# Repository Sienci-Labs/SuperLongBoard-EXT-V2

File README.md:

# SuperLongBoard EXT V2

The **SuperLongBoard EXT V2 (SLB-EXT V2)** is Sienci Labs’ next-generation CNC controller developed for the AltMill platform.

## Key Features

* grblHAL-based firmware
* Four-axis motion control
* Closed-loop stepper motor support
* USB connectivity
* SD card support
* Spindle, router and laser support
* Tool-length sensor support
* Auto-squaring
* Advanced breakout-board expansion

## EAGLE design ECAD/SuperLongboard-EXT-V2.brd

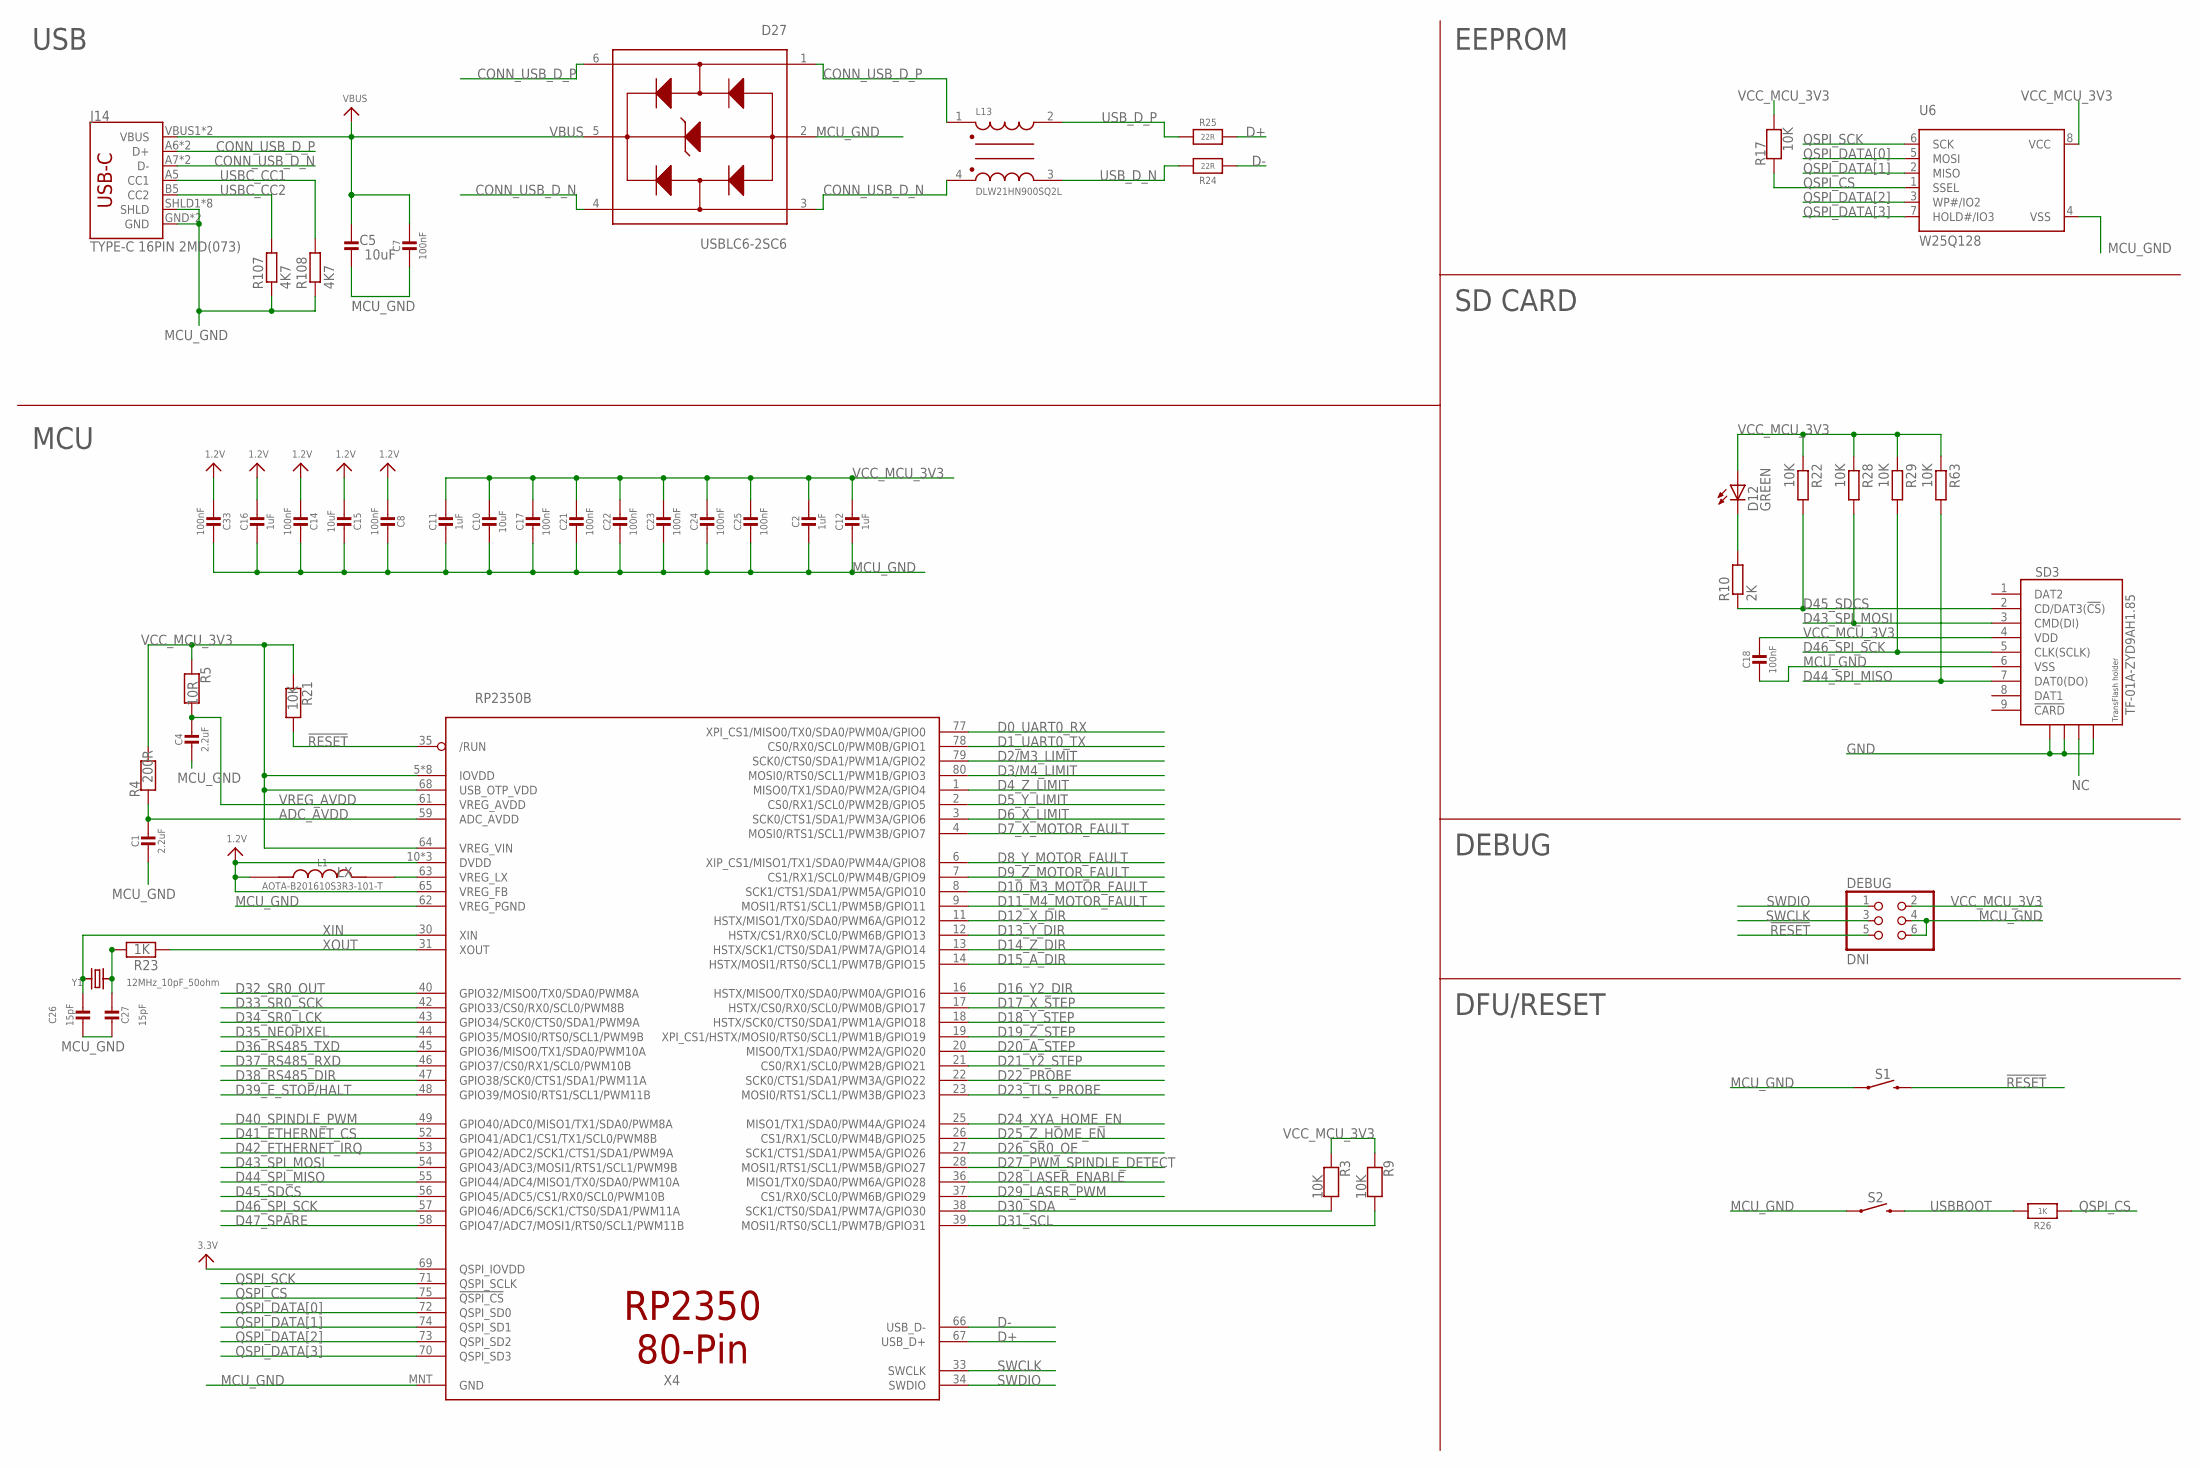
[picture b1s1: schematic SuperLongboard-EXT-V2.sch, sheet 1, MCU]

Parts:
C1, C4: 2.2uF; 0603-NO
C2, C11, C12, C16: 1uF; 0603-NO
C5, C10, C15: 10uF; _1206
C7, C8, C14, C17, C18, C21, C22, C23, C24, C25, C33: 100nF; 0603-NO
C26, C27: 15pF; 0603-NO
D12: GREEN; CHIP-LED0805
D27: USBLC6-2SC6; SOT95P280X145-6N
DEBUG: DNI; 2X03
J14: TYPE-C 16PIN 2MD(073); USB-C-16P
L1: AOTA-B201610S3R3-101-T; INDUCTOR-0806; LCSC_PART C42411119
L13: DLW21HN900SQ2L; FIL_DLW21HN900SQ2L
R3, R9: 10K; 0603-NO
R4: 200R; 0603-NO
R5: 10R; 0603-NO
R10: 2K; R0603
R17, R21: 10K; _0603
R22, R28, R29, R63: 10K; R0603
R23, R26: 1K; _0603
R24, R25: 22R; 0603-NO
R107, R108: 4K7; R0603
S1, S2: ZX-QC36-4.3TPWD; TACTILE_SWITCH_SMD_6.0X3.5MM
SD3: TF-01A-ZYD9AH1.85; TF-PULL
U6: W25Q128; SOIC8_208MIL
X4: RP2350B; QFN80
Y1: 12MHz_10pF_50ohm; CRYSTAL_3.2X2.5

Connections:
1.2V: C8.2, C14.2, C15.2, C16.1, C33.2, L1.1, X4.10 (DVDD), X4.32 (DVDD), X4.51 (DVDD), X4.65 (VREG_FB)
!RESET: DEBUG.5, R21.2, S1.2, X4.35 (/RUN)
ADC_AVDD: C1.1, R4.1, X4.59 (ADC_AVDD)
CONN_USB_D_N: D27.3 (I/O2_IN), D27.4 (I/O2_OUT), J14.A7 (D-), J14.B7 (D-), L13.4
CONN_USB_D_P: D27.1 (I/O1_IN), D27.6 (I/O1_OUT), J14.A6 (D+), J14.B6 (D+), L13.1
D0_UART0_RX: X4.77 (XPI_CS1/MISO0/TX0/SDA0/PWM0A/GPIO0); also elsewhere on the board
D1_UART0_TX: X4.78 (CS0/RX0/SCL0/PWM0B/GPIO1); also elsewhere on the board
D2/M3_LIMIT: X4.79 (SCK0/CTS0/SDA1/PWM1A/GPIO2); also elsewhere on the board
D3/M4_LIMIT: X4.80 (MOSI0/RTS0/SCL1/PWM1B/GPIO3); also elsewhere on the board
D4_Z_LIMIT: X4.1 (MISO0/TX1/SDA0/PWM2A/GPIO4); also elsewhere on the board
D5_Y_LIMIT: X4.2 (CS0/RX1/SCL0/PWM2B/GPIO5); also elsewhere on the board
D6_X_LIMIT: X4.3 (SCK0/CTS1/SDA1/PWM3A/GPIO6); also elsewhere on the board
D7_X_MOTOR_FAULT: X4.4 (MOSI0/RTS1/SCL1/PWM3B/GPIO7); also elsewhere on the board
D8_Y_MOTOR_FAULT: X4.6 (XIP_CS1/MISO1/TX1/SDA0/PWM4A/GPIO8); also elsewhere on the board
D9_Z_MOTOR_FAULT: X4.7 (CS1/RX1/SCL0/PWM4B/GPIO9); also elsewhere on the board
D10_M3_MOTOR_FAULT: X4.8 (SCK1/CTS1/SDA1/PWM5A/GPIO10); also elsewhere on the board
D11_M4_MOTOR_FAULT: X4.9 (MOSI1/RTS1/SCL1/PWM5B/GPIO11); also elsewhere on the board
D12_X_DIR: X4.11 (HSTX/MISO1/TX0/SDA0/PWM6A/GPIO12); also elsewhere on the board
D13_Y_DIR: X4.12 (HSTX/CS1/RX0/SCL0/PWM6B/GPIO13); also elsewhere on the board
D14_Z_DIR: X4.13 (HSTX/SCK1/CTS0/SDA1/PWM7A/GPIO14); also elsewhere on the board
D15_A_DIR: X4.14 (HSTX/MOSI1/RTS0/SCL1/PWM7B/GPIO15); also elsewhere on the board
D16_Y2_DIR: X4.16 (HSTX/MISO0/TX0/SDA0/PWM0A/GPIO16); also elsewhere on the board
D17_X_STEP: X4.17 (HSTX/CS0/RX0/SCL0/PWM0B/GPIO17); also elsewhere on the board
D18_Y_STEP: X4.18 (HSTX/SCK0/CTS0/SDA1/PWM1A/GPIO18); also elsewhere on the board
D19_Z_STEP: X4.19 (XPI_CS1/HSTX/MOSI0/RTS0/SCL1/PWM1B/GPIO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); also elsewhere on the board
D20_A_STEP: X4.20 (MISO0/TX1/SDA0/PWM2A/GPIO20); also elsewhere on the board
D21_Y2_STEP: X4.21 (CS0/RX1/SCL0/PWM2B/GPIO21); also elsewhere on the board
D22_PROBE: X4.22 (SCK0/CTS1/SDA1/PWM3A/GPIO22); also elsewhere on the board
D23_TLS_PROBE: X4.23 (MOSI0/RTS1/SCL1/PWM3B/GPIO23); also elsewhere on the board
D24_XYA_HOME_EN: X4.25 (MISO1/TX1/SDA0/PWM4A/GPIO24); also elsewhere on the board
D25_Z_HOME_EN: X4.26 (CS1/RX1/SCL0/PWM4B/GPIO25); also elsewhere on the board
D26_SR0_OE: X4.27 (SCK1/CTS1/SDA1/PWM5A/GPIO26); also elsewhere on the board
D27_PWM_SPINDLE_DETECT: X4.28 (MOSI1/RTS1/SCL1/PWM5B/GPIO27); also elsewhere on the board
D28_LASER_ENABLE: X4.36 (MISO1/TX0/SDA0/PWM6A/GPIO28); also elsewhere on the board
D29_LASER_PWM: X4.37 (CS1/RX0/SCL0/PWM6B/GPIO29); also elsewhere on the board
D30_SDA: R3.2, X4.38 (SCK1/CTS0/SDA1/PWM7A/GPIO30); also elsewhere on the board
D31_SCL: R9.2, X4.39 (MOSI1/RTS0/SCL1/PWM7B/GPIO31); also elsewhere on the board
D32_SR0_OUT: X4.40 (GPIO32/MISO0/TX0/SDA0/PWM8A); also elsewhere on the board
D33_SR0_SCK: X4.42 (GPIO33/CS0/RX0/SCL0/PWM8B); also elsewhere on the board
D34_SR0_LCK: X4.43 (GPIO34/SCK0/CTS0/SDA1/PWM9A); also elsewhere on the board
D35_NEOPIXEL: X4.44 (GPIO35/MOSI0/RTS0/SCL1/PWM9B); also elsewhere on the board
D36_RS485_TXD: X4.45 (GPIO36/MISO0/TX1/SDA0/PWM10A); also elsewhere on the board
D37_RS485_RXD: X4.46 (GPIO37/CS0/RX1/SCL0/PWM10B); also elsewhere on the board
D38_RS485_DIR: X4.47 (GPIO38/SCK0/CTS1/SDA1/PWM11A); also elsewhere on the board
D39_E_STOP/HALT: X4.48 (GPIO39/MOSI0/RTS1/SCL1/PWM11B); also elsewhere on the board
D40_SPINDLE_PWM: X4.49 (GPIO40/ADC0/MISO1/TX1/SDA0/PWM8A); also elsewhere on the board
D41_ETHERNET_CS: X4.52 (GPIO41/ADC1/CS1/TX1/SCL0/PWM8B); also elsewhere on the board
D42_ETHERNET_IRQ: X4.53 (GPIO42/ADC2/SCK1/CTS1/SDA1/PWM9A); also elsewhere on the board
D43_SPI_MOSI: R28.2, SD3.3 (CMD(DI)), X4.54 (GPIO43/ADC3/MOSI1/RTS1/SCL1/PWM9B); also elsewhere on the board
D44_SPI_MISO: R63.2, SD3.7 (DAT0(DO)), X4.55 (GPIO44/ADC4/MISO1/TX0/SDA0/PWM10A); also elsewhere on the board
D45_SDCS: R10.1, R22.2, SD3.2 (CD/DAT3(!CS!)), X4.56 (GPIO45/ADC5/CS1/RX0/SCL0/PWM10B)
D46_SPI_SCK: R29.2, SD3.5 (CLK(SCLK)), X4.57 (GPIO46/ADC6/SCK1/CTS0/SDA1/PWM11A); also elsewhere on the board
D47_SPARE: X4.58 (GPIO47/ADC7/MOSI1/RTS0/SCL1/PWM11B); also elsewhere on the board
D+: R25.2, X4.67 (USB_D+)
D-: R24.2, X4.66 (USB_D-)
GND: SD3.S1, SD3.S2, SD3.S4; also elsewhere on the board
LX: L1.2, X4.63 (VREG_LX)
MCU_GND: C1.2, C2.2, C4.2, C5.1, C7.2, C8.1, C10.2, C11.2, C12.2, C14.1, C15.1, C16.2, C17.2, C18.2, C21.2, C22.2, C23.2, C24.2, C25.2, C26.1, C27.1, C33.1, D27.2 (GND), DEBUG.4, DEBUG.6, J14.GND, J14.GND2 (GND), J14.SHLD1 (SHLD), J14.SHLD2 (SHLD), J14.SHLD3 (SHLD), J14.SHLD4 (SHLD), J14.SHLD5 (SHLD), J14.SHLD6 (SHLD), J14.SHLD7 (SHLD), J14.SHLD8 (SHLD), R107.1, R108.1, S1.1, S2.1, SD3.6 (VSS), U6.4 (VSS), X4.62 (VREG_PGND), X4.MNT (GND); also elsewhere on the board
unnamed: D12.C, R10.2
unnamed: C27.2, R23.1, Y1.2
NC: SD3.S3
QSPI_CS: R17.1, R26.1, U6.1 (SSEL), X4.75 (!QSPI_CS)
QSPI_DATA[0]: U6.5 (MOSI), X4.72 (QSPI_SD0)
QSPI_DATA[1]: U6.2 (MISO), X4.74 (QSPI_SD1)
QSPI_DATA[2]: U6.3 (WP#/IO2), X4.73 (QSPI_SD2)
QSPI_DATA[3]: U6.7 (HOLD#/IO3), X4.70 (QSPI_SD3)
QSPI_SCK: U6.6 (SCK), X4.71 (QSPI_SCLK)
SWCLK: DEBUG.3, X4.33 (SWCLK)
SWDIO: DEBUG.1, X4.34 (SWDIO)
USBBOOT: R26.2, S2.2
USBC_CC1: J14.A5 (CC1), R108.2
USBC_CC2: J14.B5 (CC2), R107.2
USB_D_N: L13.3, R24.1
USB_D_P: L13.2, R25.1
VBUS: C5.2, C7.1, D27.5 (VBUS), J14.VBUS1 (VBUS), J14.VBUS2 (VBUS); also elsewhere on the board
VCC_MCU_3V3: C2.1, C10.1, C11.1, C12.1, C17.1, C18.1, C21.1, C22.1, C23.1, C24.1, C25.1, D12.A, DEBUG.2, R3.1, R4.2, R5.1, R9.1, R17.2, R21.1, R22.1, R28.1, R29.1, R63.1, SD3.4 (VDD), U6.8 (VCC), X4.5 (IOVDD), X4.15 (IOVDD), X4.24 (IOVDD), X4.29 (IOVDD), X4.41 (IOVDD), X4.50 (IOVDD), X4.60 (IOVDD), X4.64 (VREG_VIN), X4.68 (USB_OTP_VDD), X4.69 (QSPI_IOVDD), X4.76 (IOVDD); also elsewhere on the board
VREG_AVDD: C4.1, R5.2, X4.61 (VREG_AVDD)
XIN: C26.2, X4.30 (XIN), Y1.1
XOUT: R23.2, X4.31 (XOUT)

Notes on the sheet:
USB
MCU
EEPROM
SD CARD
DFU/RESET
DEBUG

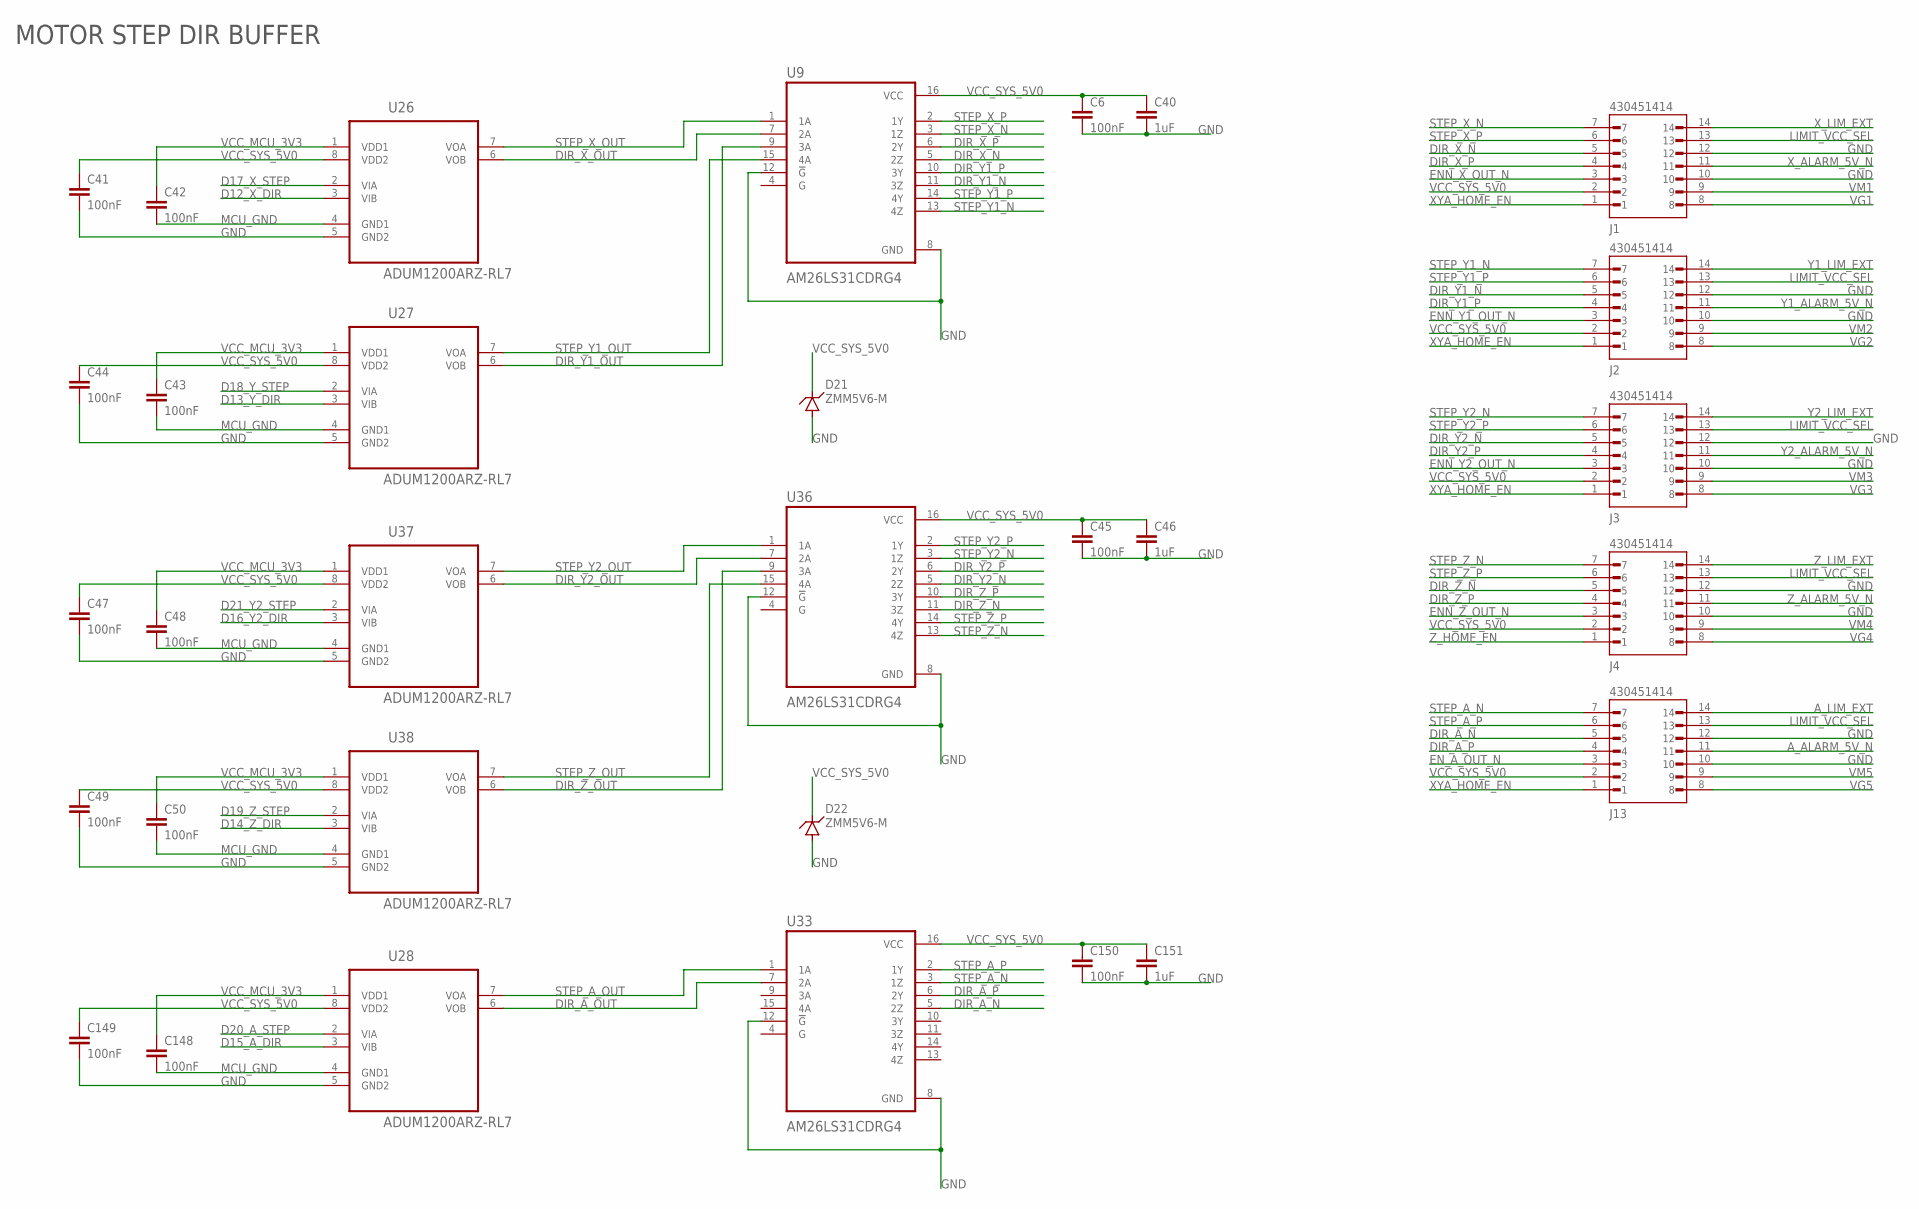
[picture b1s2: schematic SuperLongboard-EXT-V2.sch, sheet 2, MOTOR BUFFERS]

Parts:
C6, C41, C42, C43, C44, C45, C47, C48, C49, C50, C148, C149, C150: 100nF; C0603K
C40, C46, C151: 1uF; C0603K
D21, D22: ZMM5V6-M; MINIMELF
J1, J2, J3, J4, J13: 430451414; MOLEX_430451414
U9, U33, U36: AM26LS31CDRG4; SOIC127P600X175-16N
U26, U27, U28, U37, U38: ADUM1200ARZ-RL7; SOIC127P600X175-8N

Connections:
A_ALARM_5V_N: J13.11; also elsewhere on the board
A_LIM_EXT: J13.14; also elsewhere on the board
D12_X_DIR: U26.3 (VIB); also elsewhere on the board
D13_Y_DIR: U27.3 (VIB); also elsewhere on the board
D14_Z_DIR: U38.3 (VIB); also elsewhere on the board
D15_A_DIR: U28.3 (VIB); also elsewhere on the board
D16_Y2_DIR: U37.3 (VIB); also elsewhere on the board
D17_X_STEP: U26.2 (VIA); also elsewhere on the board
D18_Y_STEP: U27.2 (VIA); also elsewhere on the board
D19_Z_STEP: U38.2 (VIA); also elsewhere on the board
D20_A_STEP: U28.2 (VIA); also elsewhere on the board
D21_Y2_STEP: U37.2 (VIA); also elsewhere on the board
DIR_A_N: J13.5, U33.5 (2Z)
DIR_A_OUT: U28.6 (VOB), U33.7 (2A)
DIR_A_P: J13.4, U33.6 (2Y)
DIR_X_N: J1.5, U9.5 (2Z)
DIR_X_OUT: U9.7 (2A), U26.6 (VOB)
DIR_X_P: J1.4, U9.6 (2Y)
DIR_Y1_N: J2.5, U9.11 (3Z)
DIR_Y1_OUT: U9.9 (3A), U27.6 (VOB)
DIR_Y1_P: J2.4, U9.10 (3Y)
DIR_Y2_N: J3.5, U36.5 (2Z)
DIR_Y2_OUT: U36.7 (2A), U37.6 (VOB)
DIR_Y2_P: J3.4, U36.6 (2Y)
DIR_Z_N: J4.5, U36.11 (3Z)
DIR_Z_OUT: U36.9 (3A), U38.6 (VOB)
DIR_Z_P: J4.4, U36.10 (3Y)
ENN_X_OUT_N: J1.3; also elsewhere on the board
ENN_Y1_OUT_N: J2.3; also elsewhere on the board
ENN_Y2_OUT_N: J3.3; also elsewhere on the board
ENN_Z_OUT_N: J4.3; also elsewhere on the board
EN_A_OUT_N: J13.3; also elsewhere on the board
GND: C6.2, C40.2, C41.2, C44.2, C45.2, C46.2, C47.2, C49.2, C149.2, C150.2, C151.2, D21.A, D22.A, J1.10, J1.12, J2.10, J2.12, J3.10, J3.12, J4.10, J4.12, J13.10, J13.12, U9.8 (GND), U9.12 (!G), U26.5 (GND2), U27.5 (GND2), U28.5 (GND2), U33.8 (GND), U33.12 (!G), U36.8 (GND), U36.12 (!G), U37.5 (GND2), U38.5 (GND2); also elsewhere on the board
LIMIT_VCC_SEL: J1.13, J2.13, J3.13, J4.13, J13.13; also elsewhere on the board
MCU_GND: C42.2, C43.2, C48.2, C50.2, C148.2, U26.4 (GND1), U27.4 (GND1), U28.4 (GND1), U37.4 (GND1), U38.4 (GND1); also elsewhere on the board
STEP_A_N: J13.7, U33.3 (1Z)
STEP_A_OUT: U28.7 (VOA), U33.1 (1A)
STEP_A_P: J13.6, U33.2 (1Y)
STEP_X_N: J1.7, U9.3 (1Z)
STEP_X_OUT: U9.1 (1A), U26.7 (VOA)
STEP_X_P: J1.6, U9.2 (1Y)
STEP_Y1_N: J2.7, U9.13 (4Z)
STEP_Y1_OUT: U9.15 (4A), U27.7 (VOA)
STEP_Y1_P: J2.6, U9.14 (4Y)
STEP_Y2_N: J3.7, U36.3 (1Z)
STEP_Y2_OUT: U36.1 (1A), U37.7 (VOA)
STEP_Y2_P: J3.6, U36.2 (1Y)
STEP_Z_N: J4.7, U36.13 (4Z)
STEP_Z_OUT: U36.15 (4A), U38.7 (VOA)
STEP_Z_P: J4.6, U36.14 (4Y)
VCC_MCU_3V3: C42.1, C43.1, C48.1, C50.1, C148.1, U26.1 (VDD1), U27.1 (VDD1), U28.1 (VDD1), U37.1 (VDD1), U38.1 (VDD1); also elsewhere on the board
VCC_SYS_5V0: C6.1, C40.1, C41.1, C44.1, C45.1, C46.1, C47.1, C49.1, C149.1, C150.1, C151.1, D21.C, D22.C, J1.2, J2.2, J3.2, J4.2, J13.2, U9.16 (VCC), U26.8 (VDD2), U27.8 (VDD2), U28.8 (VDD2), U33.16 (VCC), U36.16 (VCC), U37.8 (VDD2), U38.8 (VDD2); also elsewhere on the board
VG1: J1.8; also elsewhere on the board
VG2: J2.8; also elsewhere on the board
VG3: J3.8; also elsewhere on the board
VG4: J4.8; also elsewhere on the board
VG5: J13.8; also elsewhere on the board
VM1: J1.9; also elsewhere on the board
VM2: J2.9; also elsewhere on the board
VM3: J3.9; also elsewhere on the board
VM4: J4.9; also elsewhere on the board
VM5: J13.9; also elsewhere on the board
XYA_HOME_EN: J1.1, J2.1, J3.1, J13.1; also elsewhere on the board
X_ALARM_5V_N: J1.11; also elsewhere on the board
X_LIM_EXT: J1.14; also elsewhere on the board
Y1_ALARM_5V_N: J2.11; also elsewhere on the board
Y1_LIM_EXT: J2.14; also elsewhere on the board
Y2_ALARM_5V_N: J3.11; also elsewhere on the board
Y2_LIM_EXT: J3.14; also elsewhere on the board
Z_ALARM_5V_N: J4.11; also elsewhere on the board
Z_HOME_EN: J4.1; also elsewhere on the board
Z_LIM_EXT: J4.14; also elsewhere on the board

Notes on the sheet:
MOTOR STEP DIR BUFFER

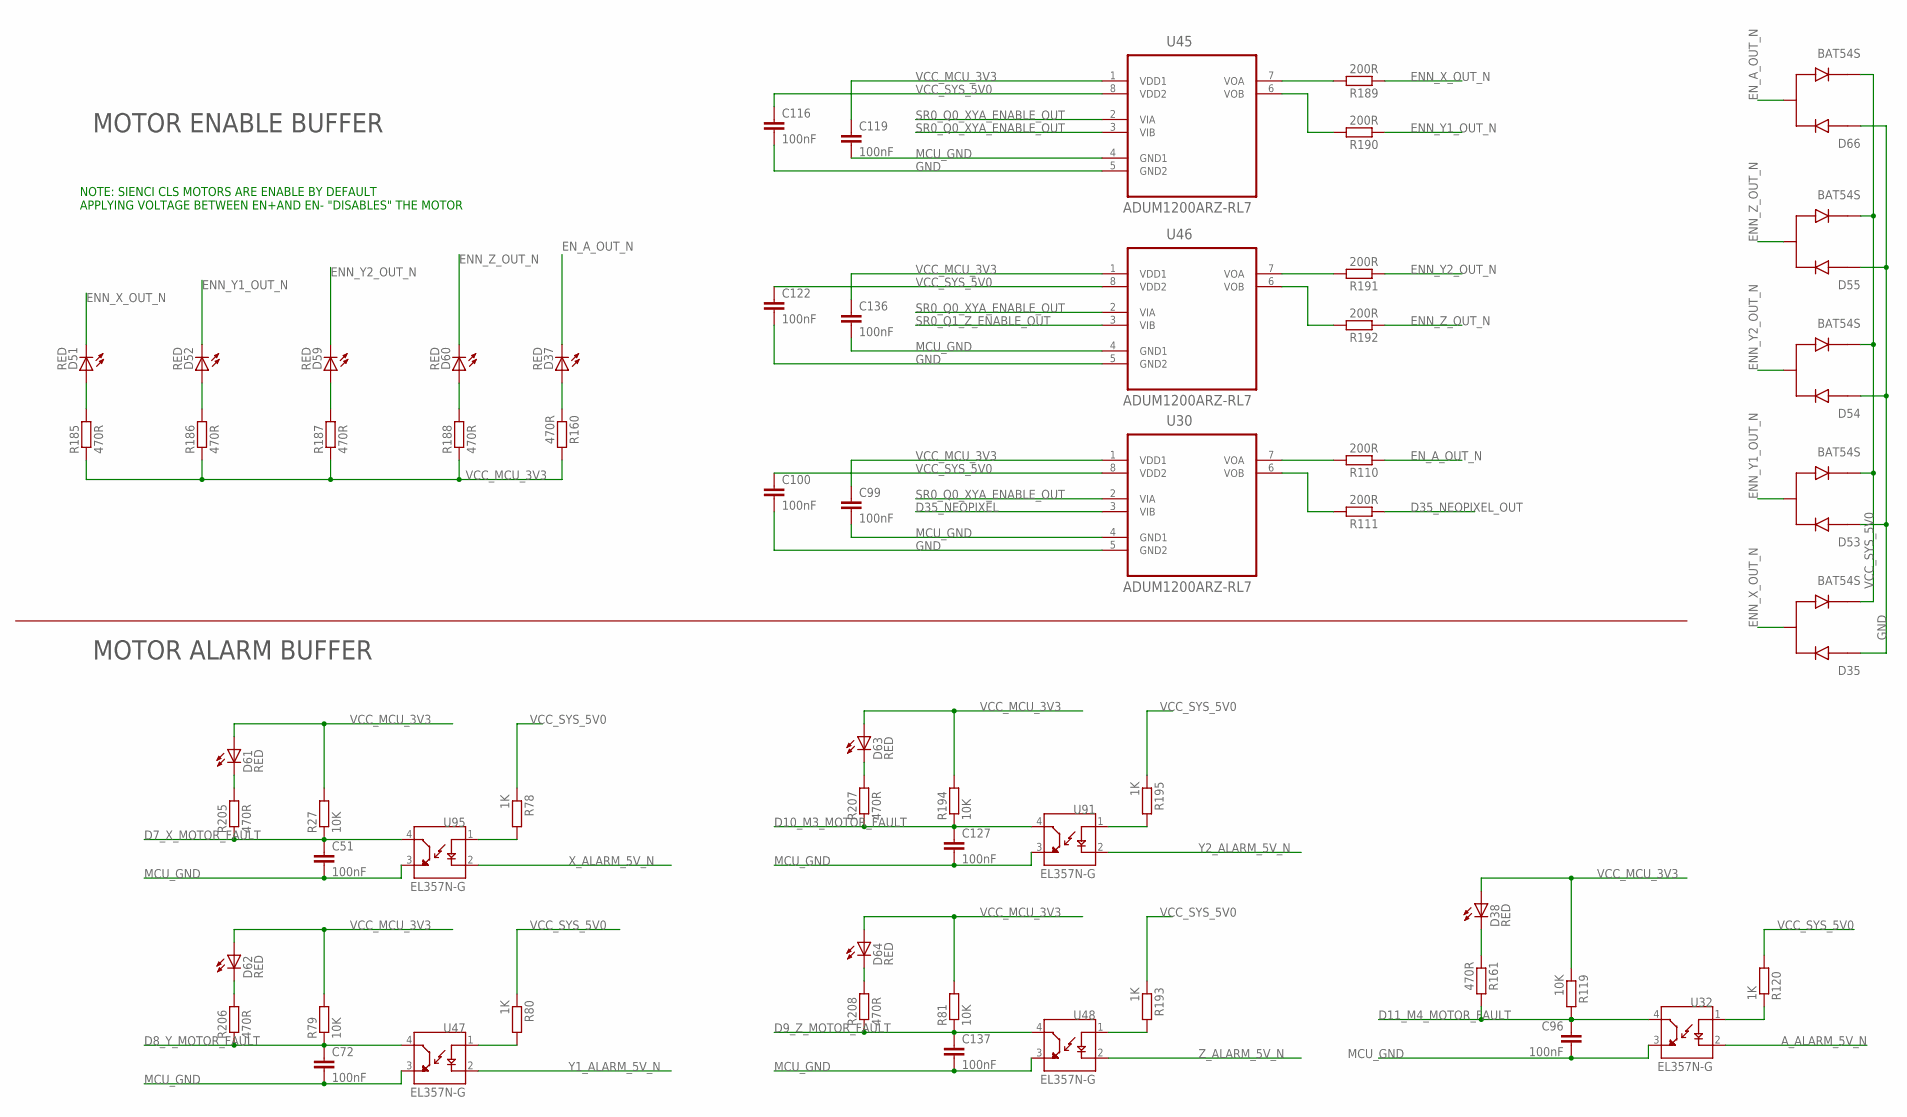
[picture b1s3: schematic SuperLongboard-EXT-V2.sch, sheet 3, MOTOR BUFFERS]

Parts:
C51, C72, C96, C127, C137: 100nF; C0603
C99, C100, C116, C119, C122, C136: 100nF; C0603K
D35, D53, D54, D55, D66: BAT54S; SOT95P240X120-3N
D37, D38, D51, D52, D59, D60, D61, D62, D63, D64: RED; CHIP-LED0805
R27, R79, R81, R119, R194: 10K; R0603
R78, R80, R120, R193, R195: 1K; R0603
R110, R111, R189, R190, R191, R192: 200R; R0603
R160, R161, R185, R186, R187, R188, R205, R206, R207, R208: 470R; R0603
U30, U45, U46: ADUM1200ARZ-RL7; SOIC127P600X175-8N
U32, U47, U48, U91, U95: EL357N-G; OPTO_EL357N-G

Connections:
A_ALARM_5V_N: U32.2 (C); also elsewhere on the board
D7_X_MOTOR_FAULT: C51.1, R27.1, R205.1, U95.4 (CT); also elsewhere on the board
D8_Y_MOTOR_FAULT: C72.1, R79.1, R206.1, U47.4 (CT); also elsewhere on the board
D9_Z_MOTOR_FAULT: C137.1, R81.1, R208.1, U48.4 (CT); also elsewhere on the board
D10_M3_MOTOR_FAULT: C127.1, R194.1, R207.1, U91.4 (CT); also elsewhere on the board
D11_M4_MOTOR_FAULT: C96.1, R119.2, R161.2, U32.4 (CT); also elsewhere on the board
D35_NEOPIXEL: U30.3 (VIB); also elsewhere on the board
D35_NEOPIXEL_OUT: R111.1; also elsewhere on the board
ENN_X_OUT_N: D35.3, D51.C, R189.1; also elsewhere on the board
ENN_Y1_OUT_N: D52.C, D53.3, R190.1; also elsewhere on the board
ENN_Y2_OUT_N: D54.3, D59.C, R191.1; also elsewhere on the board
ENN_Z_OUT_N: D55.3, D60.C, R192.1; also elsewhere on the board
EN_A_OUT_N: D37.C, D66.3, R110.1; also elsewhere on the board
GND: C100.2, C116.2, C122.2, D35.1, D53.1, D54.1, D55.1, D66.1, U30.5 (GND2), U45.5 (GND2), U46.5 (GND2); also elsewhere on the board
MCU_GND: C51.2, C72.2, C96.2, C99.2, C119.2, C127.2, C136.2, C137.2, U30.4 (GND1), U32.3 (ET), U45.4 (GND1), U46.4 (GND1), U47.3 (ET), U48.3 (ET), U91.3 (ET), U95.3 (ET); also elsewhere on the board
unnamed: R189.2, U45.7 (VOA)
unnamed: R190.2, U45.6 (VOB)
unnamed: R191.2, U46.7 (VOA)
unnamed: R192.2, U46.6 (VOB)
unnamed: D62.C, R206.2
unnamed: R78.2, U95.1 (A)
unnamed: D61.C, R205.2
unnamed: R80.2, U47.1 (A)
unnamed: D63.C, R207.2
unnamed: R195.2, U91.1 (A)
unnamed: D64.C, R208.2
unnamed: R193.2, U48.1 (A)
unnamed: D51.A, R185.2
unnamed: D52.A, R186.2
unnamed: D37.A, R160.1
unnamed: D60.A, R188.2
unnamed: D59.A, R187.2
unnamed: R110.2, U30.7 (VOA)
unnamed: R111.2, U30.6 (VOB)
unnamed: R120.1, U32.1 (A)
unnamed: D38.C, R161.1
SR0_Q0_XYA_ENABLE_OUT: U30.2 (VIA), U45.2 (VIA), U45.3 (VIB), U46.2 (VIA); also elsewhere on the board
SR0_Q1_Z_ENABLE_OUT: U46.3 (VIB); also elsewhere on the board
VCC_MCU_3V3: C99.1, C119.1, C136.1, D38.A, D61.A, D62.A, D63.A, D64.A, R27.2, R79.2, R81.2, R119.1, R160.2, R185.1, R186.1, R187.1, R188.1, R194.2, U30.1 (VDD1), U45.1 (VDD1), U46.1 (VDD1); also elsewhere on the board
VCC_SYS_5V0: C100.1, C116.1, C122.1, D35.2, D53.2, D54.2, D55.2, D66.2, R78.1, R80.1, R120.2, R193.1, R195.1, U30.8 (VDD2), U45.8 (VDD2), U46.8 (VDD2); also elsewhere on the board
X_ALARM_5V_N: U95.2 (C); also elsewhere on the board
Y1_ALARM_5V_N: U47.2 (C); also elsewhere on the board
Y2_ALARM_5V_N: U91.2 (C); also elsewhere on the board
Z_ALARM_5V_N: U48.2 (C); also elsewhere on the board

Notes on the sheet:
MOTOR ENABLE BUFFER
MOTOR ALARM BUFFER
NOTE: SIENCI CLS MOTORS ARE ENABLE BY DEFAULT APPLYING VOLTAGE BETWEEN EN+AND EN- "DISABLES" THE MOTOR

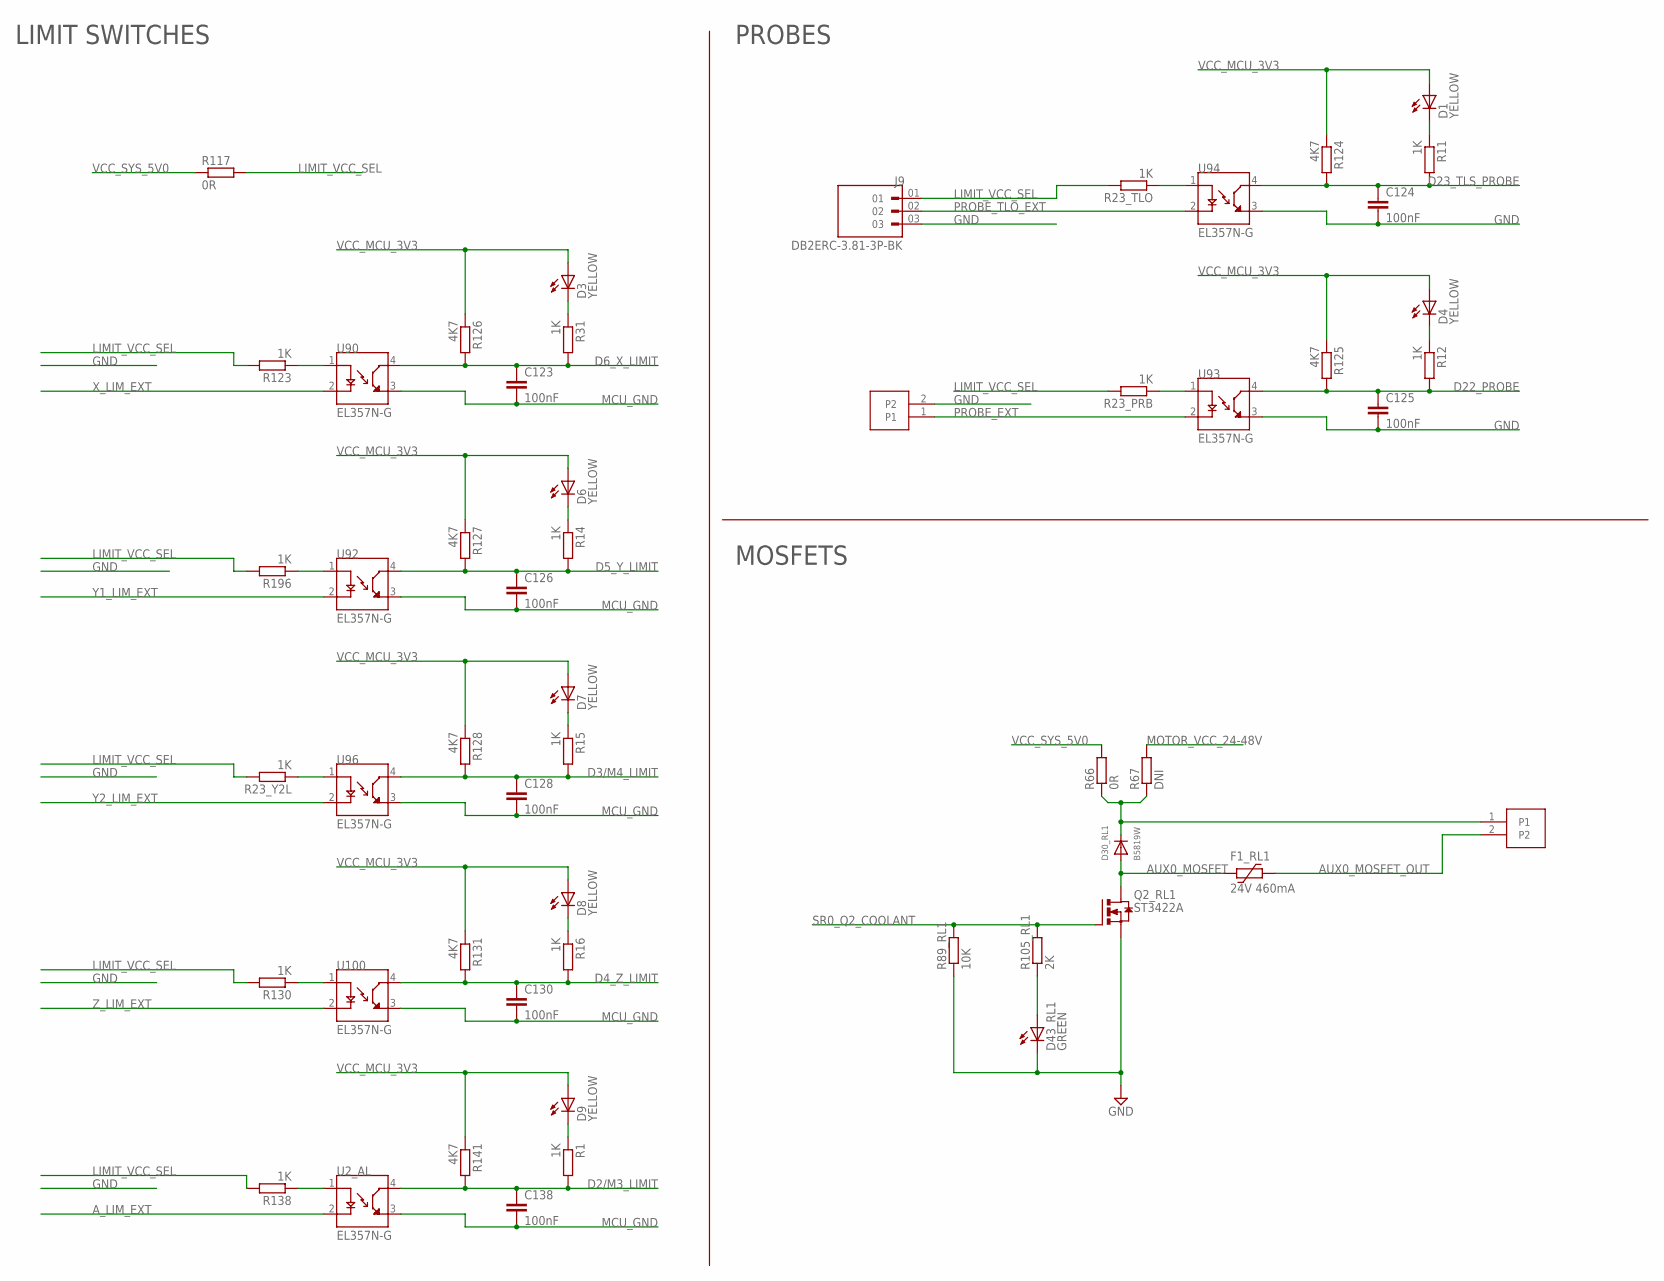
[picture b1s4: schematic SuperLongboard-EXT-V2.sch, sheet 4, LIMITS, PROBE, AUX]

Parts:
C123, C124, C125, C126, C128, C130, C138: 100nF; C0603
D1, D3, D4, D6, D7, D8, D9: YELLOW; CHIP-LED0805
D30_RL1: B5819W; SOD123FL
D43_RL1: GREEN; CHIP-LED0805
F1_RL1: 24V 460mA; 1206L
J9: DB2ERC-3.81-3P-BK; PHOENIX_1803280
J12, J17: DB2ERC-3.81-2P-BK; MC1.5/2-G-3.81
Q2_RL1: ST3422A; SOT-23
R1, R11, R12, R14, R15, R16, R23_PRB, R23_TLO, R23_Y2L, R31, R123, R130, R138, R196: 1K; R0603
R66, R117: 0R; R0603
R67: DNI; R0603
R89_RL1: 10K; R0603
R105_RL1: 2K; R0603
R124, R125, R126, R127, R128, R131, R141: 4K7; R0603
U2_AL, U90, U92, U93, U94, U96, U100: EL357N-G; OPTO_EL357N-G

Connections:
AUX0_MOSFET: D30_RL1.A, F1_RL1.2, Q2_RL1.P3 (D)
AUX0_MOSFET_OUT: F1_RL1.1, J17.2
A_LIM_EXT: U2_AL.2 (C); also elsewhere on the board
D2/M3_LIMIT: C138.1, R1.2, R141.2, U2_AL.4 (CT); also elsewhere on the board
D3/M4_LIMIT: C128.1, R15.2, R128.2, U96.4 (CT); also elsewhere on the board
D4_Z_LIMIT: C130.1, R16.2, R131.2, U100.4 (CT); also elsewhere on the board
D5_Y_LIMIT: C126.1, R14.2, R127.2, U92.4 (CT); also elsewhere on the board
D6_X_LIMIT: C123.1, R31.2, R126.2, U90.4 (CT); also elsewhere on the board
D22_PROBE: C125.1, R12.2, R125.2, U93.4 (CT); also elsewhere on the board
D23_TLS_PROBE: C124.1, R11.2, R124.2, U94.4 (CT); also elsewhere on the board
GND: C124.2, C125.2, D43_RL1.C, J9.03, J12.2, Q2_RL1.P2 (S), R89_RL1.1, U93.3 (ET), U94.3 (ET); also elsewhere on the board
LIMIT_VCC_SEL: J9.01, R23_PRB.2, R23_TLO.2, R23_Y2L.2, R117.2, R123.2, R130.2, R138.2, R196.2; also elsewhere on the board
MCU_GND: C123.2, C126.2, C128.2, C130.2, C138.2, U2_AL.3 (ET), U90.3 (ET), U92.3 (ET), U96.3 (ET), U100.3 (ET); also elsewhere on the board
MOTOR_VCC_24-48V: R67.2; also elsewhere on the board
unnamed: D3.C, R31.1
unnamed: D30_RL1.C, J17.1, R66.1, R67.1
unnamed: D43_RL1.A, R105_RL1.1
unnamed: R23_TLO.1, U94.1 (A)
unnamed: D1.C, R11.1
unnamed: R23_PRB.1, U93.1 (A)
unnamed: D4.C, R12.1
unnamed: R123.1, U90.1 (A)
unnamed: R196.1, U92.1 (A)
unnamed: D6.C, R14.1
unnamed: R23_Y2L.1, U96.1 (A)
unnamed: D7.C, R15.1
unnamed: R130.1, U100.1 (A)
unnamed: D8.C, R16.1
unnamed: R138.1, U2_AL.1 (A)
unnamed: D9.C, R1.1
PROBE_EXT: J12.1, U93.2 (C)
PROBE_TLO_EXT: J9.02, U94.2 (C)
SR0_Q2_COOLANT: Q2_RL1.P1 (G), R89_RL1.2, R105_RL1.2; also elsewhere on the board
VCC_MCU_3V3: D1.A, D3.A, D4.A, D6.A, D7.A, D8.A, D9.A, R124.1, R125.1, R126.1, R127.1, R128.1, R131.1, R141.1; also elsewhere on the board
VCC_SYS_5V0: R66.2, R117.1; also elsewhere on the board
X_LIM_EXT: U90.2 (C); also elsewhere on the board
Y1_LIM_EXT: U92.2 (C); also elsewhere on the board
Y2_LIM_EXT: U96.2 (C); also elsewhere on the board
Z_LIM_EXT: U100.2 (C); also elsewhere on the board

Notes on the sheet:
LIMIT SWITCHES
PROBES
MOSFETS

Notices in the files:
parts and their libraries:
microbuilder: This work is placed in the public domain, and may be freely used for commercial and non-commercial work with the following conditions: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
SparkFun-Jumpers: Licensing: Creative Commons ShareAlike 4.0 International - https://creativecommons.org/licenses/by-sa/4.0
